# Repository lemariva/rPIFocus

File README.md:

# Autofocus for the 16mm telephoto lens mounted on a Raspberry Pi HQ Camera.
As you may have already noticed, the Raspberry Pi HQ Camera lenses don't have any autofocus functionality. This project includes the hardware design, firmware and software to add autofocus functionality to those lenses. In this case, I use the 16mm telephoto lens.
The project is divided into two repositories. This repository includes the code of the Microservice application, whereas [lemariva/uPyFocus](https://github.com/lemariva/uPyFocus) includes the firmware for the M5Stack that controls the motors to rotate the Lens focus and aperture.

A detailed article about the application can be found on [Raspberry Pi HQ Camera: Autofocus for the Telephoto Lens (JiJi)](https://lemariva.com/blog/2020/12/raspberry-pi-hq-camera-autofocus-telephoto-lens).

## Video

## Photo examples
|          |          |          |          |
|:--------:|:--------:|:--------:|:--------:|
|||||
|Focus Type: Box <br/> Background focused (<a href="https://lemariva.com/storage/app/media/blog_imgs/hqcamera/hq_camera_background_focused.jpg">download</a>)|Focus Type: Box <br/>Nanoblock bird focused (<a href="https://lemariva.com/storage/app/media/blog_imgs/hqcamera/hq_camera_nanoblock_bird_focused.jpg">download</a>)|Focus Type: Box <br/>Nanoblock bird focused. <br/> Diff. illum & cam. aperture (<a href="https://lemariva.com/storage/app/media/blog_imgs/hqcamera/hq_camera_nanoblock_bird_focused_2.jpg">download</a>)|Focus Type: Object detector  <br/>Teddy bear focused (<a href="https://lemariva.com/storage/app/media/blog_imgs/hqcamera/hq_camera_teddy_bear_focused.jpg">download</a>)|

## Simple PCB schematic
Inside the folder `pcb`, you'll find the board design and schematic files (Eagle), to order the PCB. I added also the Gerber files that I used by <a rel="noopener noreferrer" href="https://jlcpcb.com/">jlcpcb</a>.

|          |
|:--------:|
||
|Simple PCB schematic.|

## Start the Microservices Application
The application that runs on the Raspberry Pi is a Microservices application. That means different services are orchestrated to offer an application. The orchestration is performed by docker-compose and the services are containerized using Docker.

To install Docker and `docker-compose` on the Raspberry Pi, type the following on a Terminal:
```
# Docker
curl -sSL https://get.docker.com | sh
sudo usermod -aG docker pi

# docker-compose
sudo pip3 -v install docker-compose

# usually you need these dependencies
sudo apt-get install -y libffi-dev libssl-dev
sudo apt-get install -y python3 python3-pip
sudo apt-get remove python-configparser
```

The services of the microservices application are the following:
* **webapp**: it provides the frontend application (webserver). It is programmed in Angular.
* **backend**: it communicates with the frontend via a RestAPI (Flask server), controls the camera, sends the signals to the M5Stack to control the motors, sends the signals and data to the other services to identify objects and take photos. Basically, it is the core service. It is programmed in Python.
* **obj-detector**: it receives an image over UDP and identifies the object on it and returns a JSON message. It is programmed in Python. It uses TensorFlow and connects to the Coral USB Accelerator to process the data in real-time.
* **photo-service**: it receives a signal via RestAPI (Flask server) to take photos and it processes them to create HDR photos. It is programmed in Python and it uses Celery for multitasking/non-blocking response to the RestAPI.
* **redis**: Celery uses this service to schedule the tasks.

To start the Microservices application, follow these steps:
1. Download the `docker-compose.yml` file or just clone the complete [lemariva/rPIFocus](https://github.com/lemariva/rPIFocus) repository:
    ```sh
    git clone https://github.com/lemariva/rPIFocus.git
    ```
2. Open the `docker-compose.yml` file and change the `HOST_M5STACK=<ip-address>` with the IP of your M5Stack.
3. Start the application by typing inside the `rPiFocus` folder:
    ```sh
    docker-compose up -d
    ```
4. Open a browser and visit the URL address: `http://<ip-raspberrypi>:4200`, you'll see an interface like in the figure below. ( shhh... I've just noticed that I wrote Raspberry HD camera and not HQ camera... :( )
5. To stop the application, type:
    ```sh
    docker-compose down
    ```

|           |
|:---------:|
||
|Webservice Microservices Application|

## Build containers
The Docker images can be built by typing e.g.:
```sh
docker build -t <your-docker-hub-name>/rpifocus-webapp:1.0.0 webapp
```
Then, if you are logged in into Docker Hub, you can push the image by typing:
```sh
docker push <your-docker-hub-name>/webapp
# read this tutorial: https://docs.docker.com/docker-hub/access-tokens/#create-an-access-token for login
```

Then, you need to edit the image names inside the `docker-compose.yml` and start the microservices application again (`docker-compose down` and then `docker-compose up -d`).

Additionally, I included a `cloudbuild.yaml` file inside each folder. This can be used to build those images using Google Cloud Build. In this article: [M5Stack: Fresh air checker can help you to stay safe from #COVID-19](https://lemariva.com/blog/2020/11/m5stack-fresh-air-helps-stay-safe-from-covid-19), you can find an example of how to do that!

## License
* GNU General Public License v3.0

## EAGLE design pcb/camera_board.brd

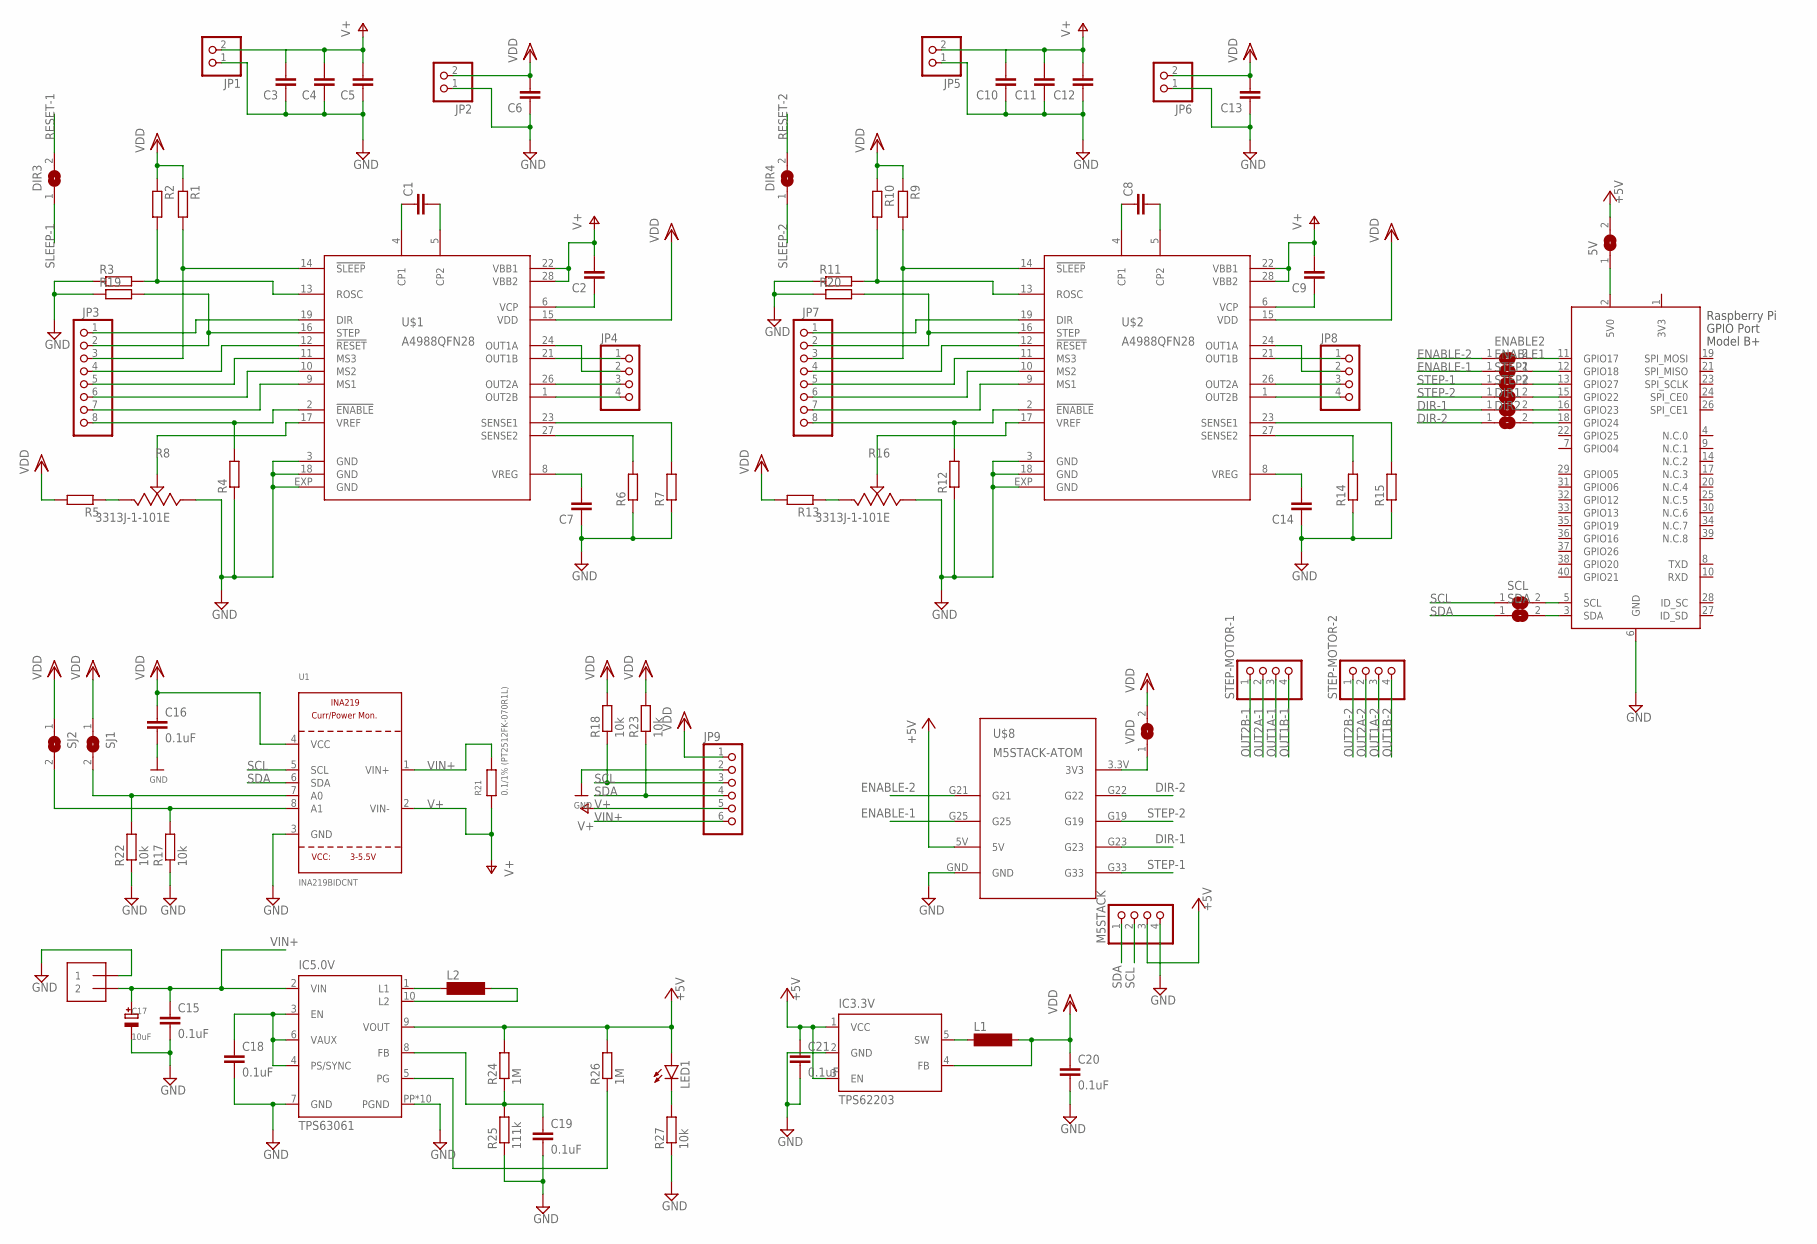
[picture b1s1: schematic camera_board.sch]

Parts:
5V: SOLDERJUMPERREFLOW_NOPASTE; SOLDERJUMPER_REFLOW_NOPASTE
7.5V: TERMBLOCK_1X2-3.5MM; 1X2-3.5MM
C1, C2, C4, C5, C6, C7, C8, C9, C11, C12, C13, C14: C-EUC0402; C0402
C3, C10: C-EUC1206; C1206
C15, C18, C19, C20, C21: 0.1uF; C0805
C16: 0.1uF; C0402
C17: 10uF; PANASONIC_C
DIR1, DIR2, DIR3, DIR4: SOLDERJUMPERREFLOW_NOPASTE; SOLDERJUMPER_REFLOW_NOPASTE
ENABLE1, ENABLE2: SOLDERJUMPERREFLOW_NOPASTE; SOLDERJUMPER_REFLOW_NOPASTE
IC3.3V: TPS62203; SOT23-5
IC5.0V: TPS63061; DSC-S-PWSON-N10
JP1, JP2, JP5, JP6: PINHD-1X2; 1X02
JP3, JP7: PINHD-1X8; 1X08
JP4, JP8: PINHD-1X4; 1X04
JP9: HEADER-1X670MIL; 1X06_ROUND_70
L1, L2: MS50
LED1: LEDCHIPLED_0603; CHIPLED_0603
M5STACK: PINHD-1X4; 1X04
R1, R2, R3, R4, R5, R9, R10, R11, R12, R13: R-EU_R0402; R0402
R6, R7, R14, R15: R-EU_R0603; R0603
R8, R16: 3313J-1-101E
R17, R18, R22, R23, R27: 10k; R0603
R19, R20: R-EU_R0805; R0805
R21: 0.1/1% (PT2512FK-070R1L); R2512
R24, R26: 1M; R0603
R25: 111k; R0603
SCL: SOLDERJUMPERREFLOW_NOPASTE; SOLDERJUMPER_REFLOW_NOPASTE
SDA: SOLDERJUMPERREFLOW_NOPASTE; SOLDERJUMPER_REFLOW_NOPASTE
SJ1, SJ2: SOLDERJUMPERREFLOW_NOPASTE; SOLDERJUMPER_REFLOW_NOPASTE
STEP1, STEP2: SOLDERJUMPERREFLOW_NOPASTE; SOLDERJUMPER_REFLOW_NOPASTE
STEP-MOTOR-1, STEP-MOTOR-2: PINHD-1X4; 1X04
U1: INA219BIDCNT; SOT23-8
U$1, U$2: A4988QFN28; QFN28-ML_6X6MM
U$8: M5STACK-ATOM
VDD: SOLDERJUMPERREFLOW_NOPASTE; SOLDERJUMPER_REFLOW_NOPASTE
X1: RASPI_BOARD_B+_E4; RASPI_BOARD_B+_EDGES_4DRILL

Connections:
3V3: X1.1 (3V3)
+5V: 5V.2, C21.1, IC3.3V.1 (VCC), IC3.3V.3 (EN), IC5.0V.9 (VOUT), LED1.A, M5STACK.3, R24.2, R26.2, U$8.5V
DIR-1: DIR1.1, JP3.1, U$1.19 (DIR), U$8.G23
DIR-2: DIR2.1, JP7.1, U$2.19 (DIR), U$8.G22
ENABLE-1: ENABLE1.1, JP3.8, R4.2, U$1.2 (!ENABLE), U$8.G25
ENABLE-2: ENABLE2.1, JP7.8, R12.2, U$2.2 (!ENABLE), U$8.G21
GND: 7.5V.1, C3.1, C4.1, C5.1, C6.1, C7.1, C10.1, C11.1, C12.1, C13.1, C14.1, C15.2, C16.2, C17.-, C18.2, C19.2, C20.2, C21.2, IC3.3V.2 (GND), IC5.0V.7 (GND), IC5.0V.PP (PGND), IC5.0V.PP@1 (PGND), IC5.0V.PP@2 (PGND), IC5.0V.PP@3 (PGND), IC5.0V.PP@4 (PGND), IC5.0V.PP@5 (PGND), IC5.0V.PP@7 (PGND), IC5.0V.PP@8 (PGND), IC5.0V.PP@9 (PGND), IC5.0V.PP@10 (PGND), JP1.1, JP2.1, JP5.1, JP6.1, JP9.2, M5STACK.4, R3.1, R4.1, R6.1, R7.1, R8.3, R11.1, R12.1, R14.1, R15.1, R16.3, R17.1, R19.1, R20.1, R22.1, R25.1, R27.1, U1.3 (GND), U$1.3 (GND), U$1.18 (GND), U$1.EXP (GND), U$2.3 (GND), U$2.18 (GND), U$2.EXP (GND), U$8.GND, X1.6 (GND)
unnamed: R2.2, R3.2, U$1.13 (ROSC)
unnamed: ENABLE2.2, X1.11 (GPIO17)
unnamed: JP3.5, U$1.11 (MS3)
unnamed: C18.1, IC5.0V.3 (EN), IC5.0V.4 (PS/SYNC), IC5.0V.6 (VAUX)
unnamed: IC5.0V.1 (L1), L2.1
unnamed: IC5.0V.10 (L2), L2.2
unnamed: JP3.6, U$1.10 (MS2)
unnamed: JP3.7, U$1.9 (MS1)
unnamed: C19.1, IC5.0V.8 (FB), R24.1, R25.2
unnamed: R8.2, U$1.17 (VREF)
unnamed: R5.1, R8.1
unnamed: C2.1, U$1.6 (VCP)
unnamed: C7.2, U$1.8 (VREG)
unnamed: 5V.1, X1.2 (5V0)
unnamed: ENABLE1.2, X1.12 (GPIO18)
unnamed: IC5.0V.5 (PG), R26.1
unnamed: STEP1.2, X1.13 (GPIO27)
unnamed: R7.2, U$1.23 (SENSE1)
unnamed: R6.2, U$1.27 (SENSE2)
unnamed: C1.2, U$1.5 (CP2)
unnamed: C1.1, U$1.4 (CP1)
unnamed: R10.2, R11.2, U$2.13 (ROSC)
unnamed: STEP2.2, X1.15 (GPIO22)
unnamed: DIR1.2, X1.16 (GPIO23)
unnamed: DIR2.2, X1.18 (GPIO24)
unnamed: SCL.2, X1.5 (SCL)
unnamed: JP7.5, U$2.11 (MS3)
unnamed: JP7.6, U$2.10 (MS2)
unnamed: JP7.7, U$2.9 (MS1)
unnamed: SDA.2, X1.3 (SDA)
unnamed: R13.1, R16.1
unnamed: R16.2, U$2.17 (VREF)
unnamed: C9.1, U$2.6 (VCP)
unnamed: IC3.3V.5 (SW), L1.1
unnamed: LED1.C, R27.2
unnamed: U$8.3.3V (3V3), VDD.1
unnamed: R15.2, U$2.23 (SENSE1)
unnamed: R14.2, U$2.27 (SENSE2)
unnamed: C14.2, U$2.8 (VREG)
unnamed: C8.2, U$2.5 (CP2)
unnamed: C8.1, U$2.4 (CP1)
unnamed: R17.2, SJ2.2, U1.8 (A1)
unnamed: R22.2, SJ1.2, U1.7 (A0)
OUT1A-1: JP4.2, STEP-MOTOR-1.3, U$1.24 (OUT1A)
OUT1A-2: JP8.2, STEP-MOTOR-2.3, U$2.24 (OUT1A)
OUT1B-1: JP4.1, STEP-MOTOR-1.4, U$1.21 (OUT1B)
OUT1B-2: JP8.1, STEP-MOTOR-2.4, U$2.21 (OUT1B)
OUT2A-1: JP4.3, STEP-MOTOR-1.2, U$1.26 (OUT2A)
OUT2A-2: JP8.3, STEP-MOTOR-2.2, U$2.26 (OUT2A)
OUT2B-1: JP4.4, STEP-MOTOR-1.1, U$1.1 (OUT2B)
OUT2B-2: JP8.4, STEP-MOTOR-2.1, U$2.1 (OUT2B)
RESET-1: DIR3.2, JP3.4, U$1.12 (!RESET)
RESET-2: DIR4.2, JP7.4, U$2.12 (!RESET)
SCL: JP9.3, M5STACK.2, R18.1, SCL.1, U1.5 (SCL)
SDA: JP9.4, M5STACK.1, R23.1, SDA.1, U1.6 (SDA)
SLEEP-1: DIR3.1, JP3.3, R1.2, U$1.14 (!SLEEP)
SLEEP-2: DIR4.1, JP7.3, R9.2, U$2.14 (!SLEEP)
STEP-1: JP3.2, R19.2, STEP1.1, U$1.16 (STEP), U$8.G33
STEP-2: JP7.2, R20.2, STEP2.1, U$2.16 (STEP), U$8.G19
V+: C2.2, C3.2, C4.2, C5.2, C9.2, C10.2, C11.2, C12.2, JP1.2, JP5.2, JP9.5, R21.1, U1.2 (VIN-), U$1.22 (VBB1), U$1.28 (VBB2), U$2.22 (VBB1), U$2.28 (VBB2)
VDD: C6.2, C13.2, C16.1, C20.1, IC3.3V.4 (FB), JP2.2, JP6.2, JP9.1, L1.2, R1.1, R2.1, R5.2, R9.1, R10.1, R13.2, R18.2, R23.2, SJ1.1, SJ2.1, U1.4 (VCC), U$1.15 (VDD), U$2.15 (VDD), VDD.2
VIN+: 7.5V.2, C15.1, C17.+, IC5.0V.2 (VIN), JP9.6, R21.2, U1.1 (VIN+)

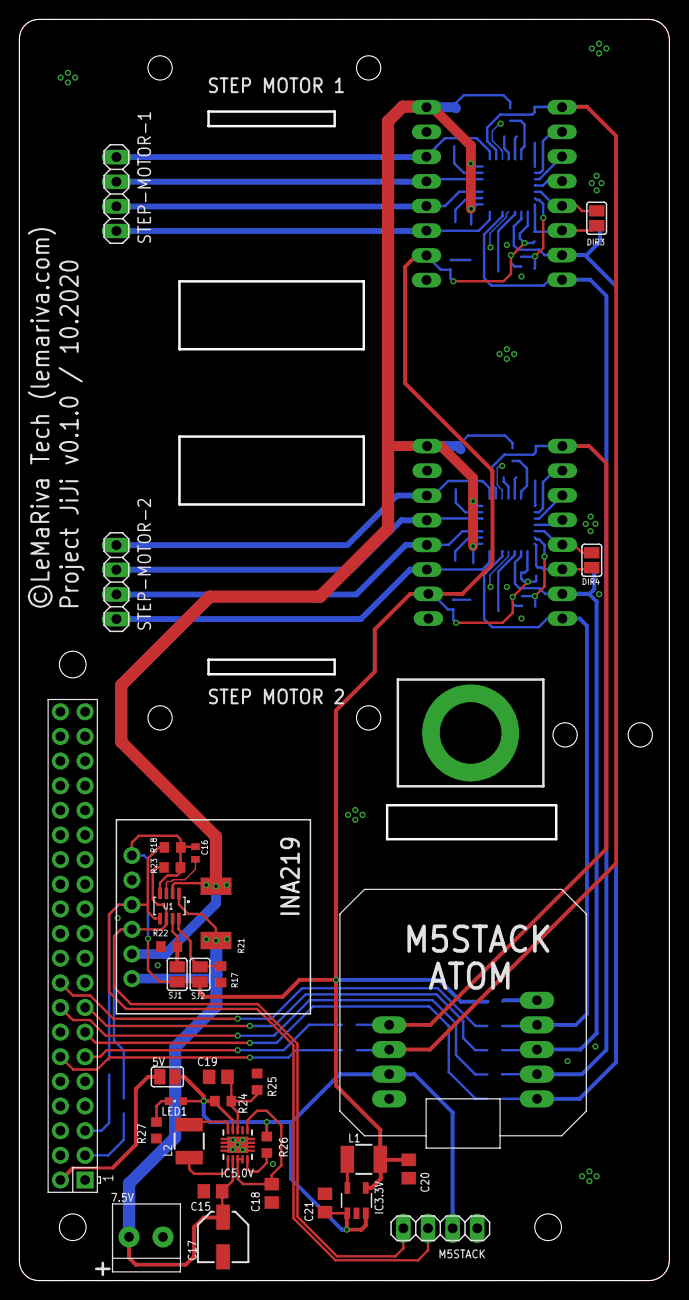
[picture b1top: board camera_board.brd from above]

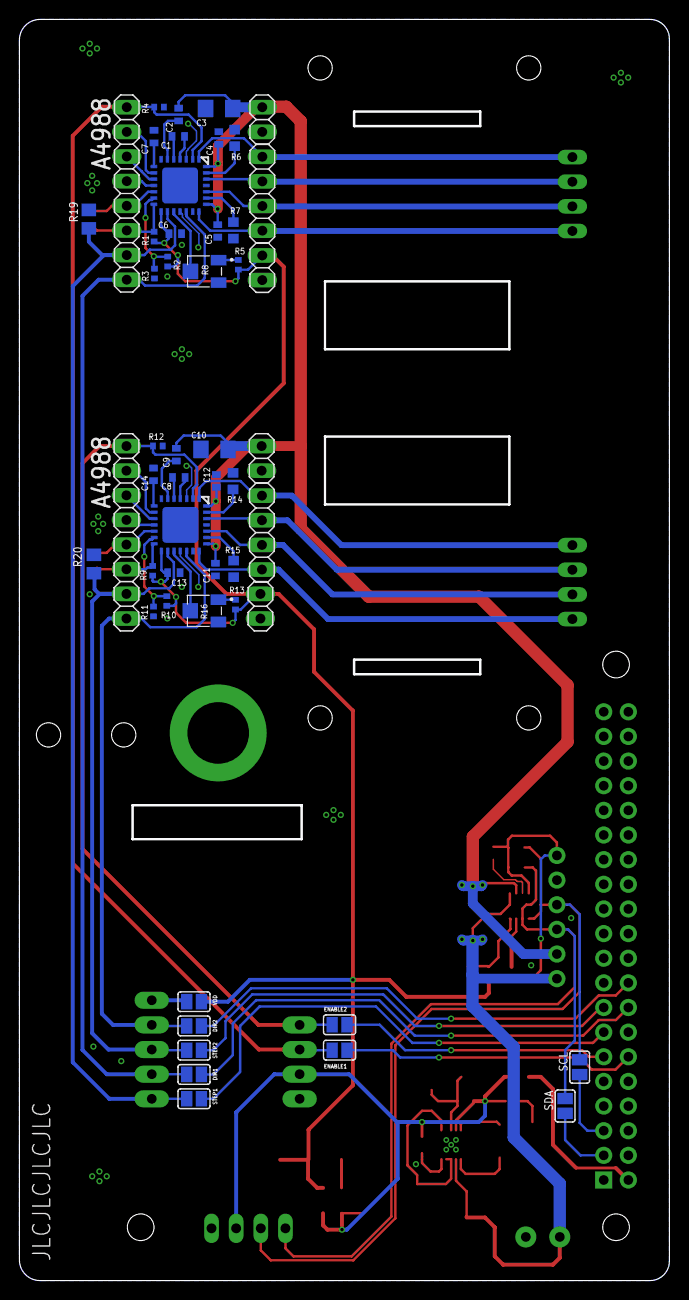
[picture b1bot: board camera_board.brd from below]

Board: 2 copper layers, 66.7 x 129.7 mm, 85 parts (51 on the bottom side), 68 nets.

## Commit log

2020-11-01 initial commit (after cleaned up) - microservices still not checked
2020-11-01 changed to backend (docker-compose service name)
2020-11-01 added bus for coral usb accelerator
2020-11-01 added symbolic link for ng
2020-11-01 added more needed libraries and cleaned up
2020-11-07 backend working as a microservice
2020-11-07 added license
2020-11-08 added env. vars on supervisord.conf
2020-11-08 added cv2 requirements
2020-11-08 minor error correction
2020-11-08 fix version and paths
2020-11-08 changed style & template of the gallery
2020-12-25 cleaning gallery and added gitkeep files
2020-12-25 added better gallery style
2020-12-25 (hotfix) solved slow update from streaming because of proxy
2020-12-25 (hotfix) replaced wrong video feed url
2020-12-25 app cleaned up and optimized
2020-12-25 (feat) added external config of element identification
2020-12-26 (hotfix) port for backend and restart for redis added
2020-12-30 cleaned up
2020-12-31 renamed docker image to go public
2020-12-31 added board design and schematic as PDF files
2020-12-31 added jlcpcb gerber files
2020-12-31 typo
2021-01-23 upgraded edgetpu library

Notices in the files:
pcb/camera_board.brd:
©LeMaRiva Tech (lemariva.com)
